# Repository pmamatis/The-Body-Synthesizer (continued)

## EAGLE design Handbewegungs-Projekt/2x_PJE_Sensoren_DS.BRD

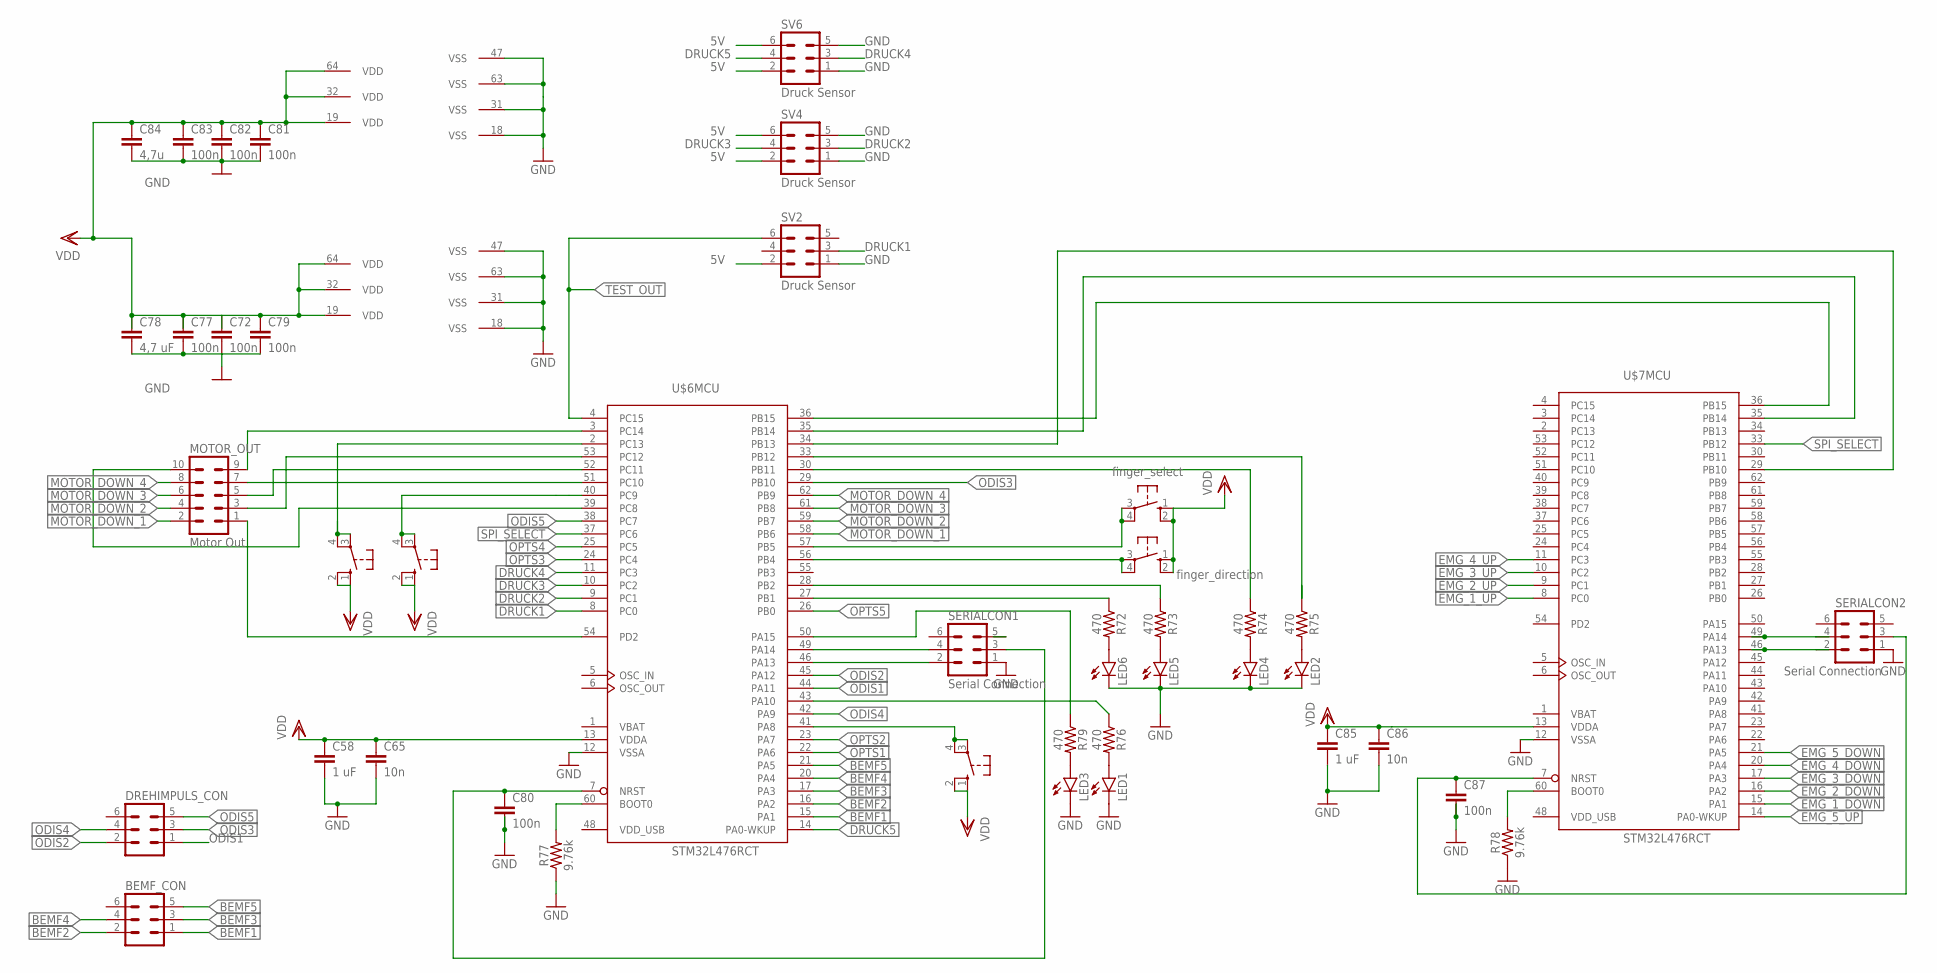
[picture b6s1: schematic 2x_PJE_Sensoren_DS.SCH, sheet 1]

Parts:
BEMF_CON: ML6
BUTTON: 10-XX; B3F-10XX
C58, C85: 1 uF; C0603
C65, C86: 10n; C0603
C72, C77, C79, C80, C81, C82, C83, C87: 100n; C0603
C78: 4,7 uF; C0603
C84: 4,7u; C0603
DREHIMPULS_CON: ML6
FINGER_DIRECTION: finger_direction; B3F-10XX
FINGER_SELECT: finger_select; B3F-10XX
LEARN: 10-XX; B3F-10XX
LEARN_STOP: 10-XX; B3F-10XX
LED1, LED2, LED3, LED4, LED5, LED6: LEDCHIP-LED0603; CHIP-LED0603
MOTOR_OUT: Motor Out; ML10
R72, R73, R74, R75, R76, R79: 470; 0603
R77, R78: 9.76k; 0603
SERIALCON1, SERIALCON2: Serial Connection; ML6
SV2, SV4, SV6: Druck Sensor; ML6
U$6, U$7: STM32L476RCT; LQFP64

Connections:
5V: SV2.2, SV4.2, SV4.6, SV6.2, SV6.6; also elsewhere on the board
BEMF1: BEMF_CON.1, U$6.15 (PA1)
BEMF2: BEMF_CON.2, U$6.16 (PA2)
BEMF3: BEMF_CON.3, U$6.17 (PA3)
BEMF4: BEMF_CON.4, U$6.20 (PA4)
BEMF5: BEMF_CON.5, U$6.21 (PA5)
DRUCK1: SV2.3, U$6.8 (PC0)
DRUCK2: SV4.3, U$6.9 (PC1)
DRUCK3: SV4.4, U$6.10 (PC2)
DRUCK4: SV6.3, U$6.11 (PC3)
DRUCK5: SV6.4, U$6.14 (PA0-WKUP)
EMG_1_DOWN: U$7.15 (PA1); also elsewhere on the board
EMG_1_UP: U$7.8 (PC0); also elsewhere on the board
EMG_2_DOWN: U$7.16 (PA2); also elsewhere on the board
EMG_2_UP: U$7.9 (PC1); also elsewhere on the board
EMG_3_DOWN: U$7.17 (PA3); also elsewhere on the board
EMG_3_UP: U$7.10 (PC2); also elsewhere on the board
EMG_4_DOWN: U$7.20 (PA4)
EMG_4_UP: U$7.11 (PC3)
EMG_5_DOWN: U$7.21 (PA5)
EMG_5_UP: U$7.14 (PA0-WKUP)
GND: C58.2, C65.2, C72.2, C77.2, C78.2, C79.2, C80.2, C81.2, C82.2, C83.2, C84.2, C85.2, C86.2, C87.2, LED1.C, LED2.C, LED3.C, LED4.C, LED5.C, LED6.C, R77.1, R78.1, SERIALCON1.1, SERIALCON2.1, SV2.1, SV4.1, SV4.5, SV6.1, SV6.5, U$6.12 (VSSA), U$6.18 (VSS), U$6.31 (VSS), U$6.47 (VSS), U$6.63 (VSS), U$7.12 (VSSA), U$7.18 (VSS), U$7.31 (VSS), U$7.47 (VSS), U$7.63 (VSS); also elsewhere on the board
LEARN: LEARN.3, LEARN.4 (P1), U$6.41 (PA8)
LEARN1: BUTTON.3, BUTTON.4 (P1), U$6.2 (PC13)
LEARN_STOP: LEARN_STOP.3, LEARN_STOP.4 (P1), U$6.40 (PC9)
LED1: R72.1, U$6.27 (PB1)
LED2: R73.1, U$6.28 (PB2)
LED4: R74.1, U$6.30 (PB11)
LED5: R75.1, U$6.33 (PB12)
MISO: U$6.35 (PB14), U$7.35 (PB14)
MOSI: U$6.36 (PB15), U$7.36 (PB15)
MOTOR_DOWN_1: MOTOR_OUT.2, U$6.58 (PB6)
MOTOR_DOWN_2: MOTOR_OUT.4, U$6.59 (PB7)
MOTOR_DOWN_3: MOTOR_OUT.6, U$6.61 (PB8)
MOTOR_DOWN_4: MOTOR_OUT.8, U$6.62 (PB9)
MOTOR_DOWN_5: MOTOR_OUT.10, U$6.39 (PC8)
MOTOR_UP5: MOTOR_OUT.9, U$6.3 (PC14)
MOTOR_UP_1: MOTOR_OUT.1, U$6.54 (PD2)
MOTOR_UP_2: MOTOR_OUT.3, U$6.53 (PC12)
MOTOR_UP_3: MOTOR_OUT.5, U$6.52 (PC11)
MOTOR_UP_4: MOTOR_OUT.7, U$6.51 (PC10)
unnamed: LED6.A, R72.2
unnamed: LED5.A, R73.2
unnamed: LED4.A, R74.2
unnamed: LED2.A, R75.2
unnamed: LED3.A, R79.2
unnamed: LED1.A, R76.2
unnamed: R76.1, U$6.43 (PA10)
unnamed: FINGER_DIRECTION.3, FINGER_DIRECTION.4 (P1), U$6.56 (PB4)
unnamed: FINGER_SELECT.3, FINGER_SELECT.4 (P1), U$6.57 (PB5)
unnamed: SERIALCON1.4, U$6.49 (PA14)
unnamed: SERIALCON1.2, U$6.46 (PA13)
unnamed: R77.2, U$6.60 (BOOT0)
unnamed: R78.2, U$7.60 (BOOT0)
unnamed: R79.1, U$6.50 (PA15)
NRST1: C80.1, SERIALCON1.3, U$6.7 (NRST)
NRST2: C87.1, SERIALCON2.3, U$7.7 (NRST)
ODIS1: DREHIMPULS_CON.1, U$6.44 (PA11)
ODIS2: DREHIMPULS_CON.2, U$6.45 (PA12)
ODIS3: DREHIMPULS_CON.3, U$6.29 (PB10)
ODIS4: DREHIMPULS_CON.4, U$6.42 (PA9)
ODIS5: DREHIMPULS_CON.5, U$6.38 (PC7)
OPTS1: U$6.22 (PA6); also elsewhere on the board
OPTS2: U$6.23 (PA7); also elsewhere on the board
OPTS3: U$6.24 (PC4); also elsewhere on the board
OPTS4: U$6.25 (PC5); also elsewhere on the board
OPTS5: U$6.26 (PB0); also elsewhere on the board
SPI_CLK: U$6.34 (PB13), U$7.29 (PB10)
SPI_SELECT: U$6.37 (PC6), U$7.33 (PB12)
TCK2: SERIALCON2.4, U$7.49 (PA14)
TEST_OUT: SV2.6, U$6.4 (PC15)
TMS2: SERIALCON2.2, U$7.46 (PA13)
VBAT: U$6.1 (VBAT), U$7.1 (VBAT)
VDD: BUTTON.1 (S), BUTTON.2 (S1), C58.1, C65.1, C72.1, C77.1, C78.1, C79.1, C81.1, C82.1, C83.1, C84.1, C85.1, C86.1, FINGER_DIRECTION.1 (S), FINGER_DIRECTION.2 (S1), FINGER_SELECT.1 (S), FINGER_SELECT.2 (S1), LEARN.1 (S), LEARN.2 (S1), LEARN_STOP.1 (S), LEARN_STOP.2 (S1), U$6.13 (VDDA), U$6.19 (VDD), U$6.32 (VDD), U$6.64 (VDD), U$7.13 (VDDA), U$7.19 (VDD), U$7.32 (VDD), U$7.64 (VDD); also elsewhere on the board
VDD_USB: U$6.48 (VDD_USB), U$7.48 (VDD_USB)

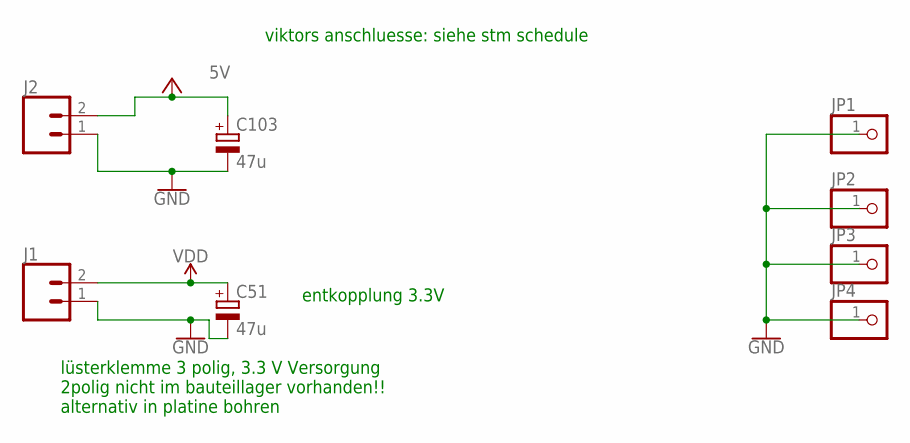
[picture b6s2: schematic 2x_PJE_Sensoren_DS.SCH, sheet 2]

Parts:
C51, C103: 47u; TAP5-70
J1, J2: CONN_02POLAR; MOLEX-1X2
JP1, JP2, JP3, JP4: PINHD-1X1; 1X01

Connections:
5V: C103.+, J2.2; also elsewhere on the board
GND: C51.-, C103.-, J1.1, J2.1, JP1.1, JP2.1, JP3.1, JP4.1; also elsewhere on the board
VDD: C51.+, J1.2; also elsewhere on the board

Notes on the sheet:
viktors anschluesse: siehe stm schedule
entkopplung 3.3V
lüsterklemme 3 polig, 3.3 V Versorgung 2polig nicht im bauteillager vorhanden!! alternativ in platine bohren

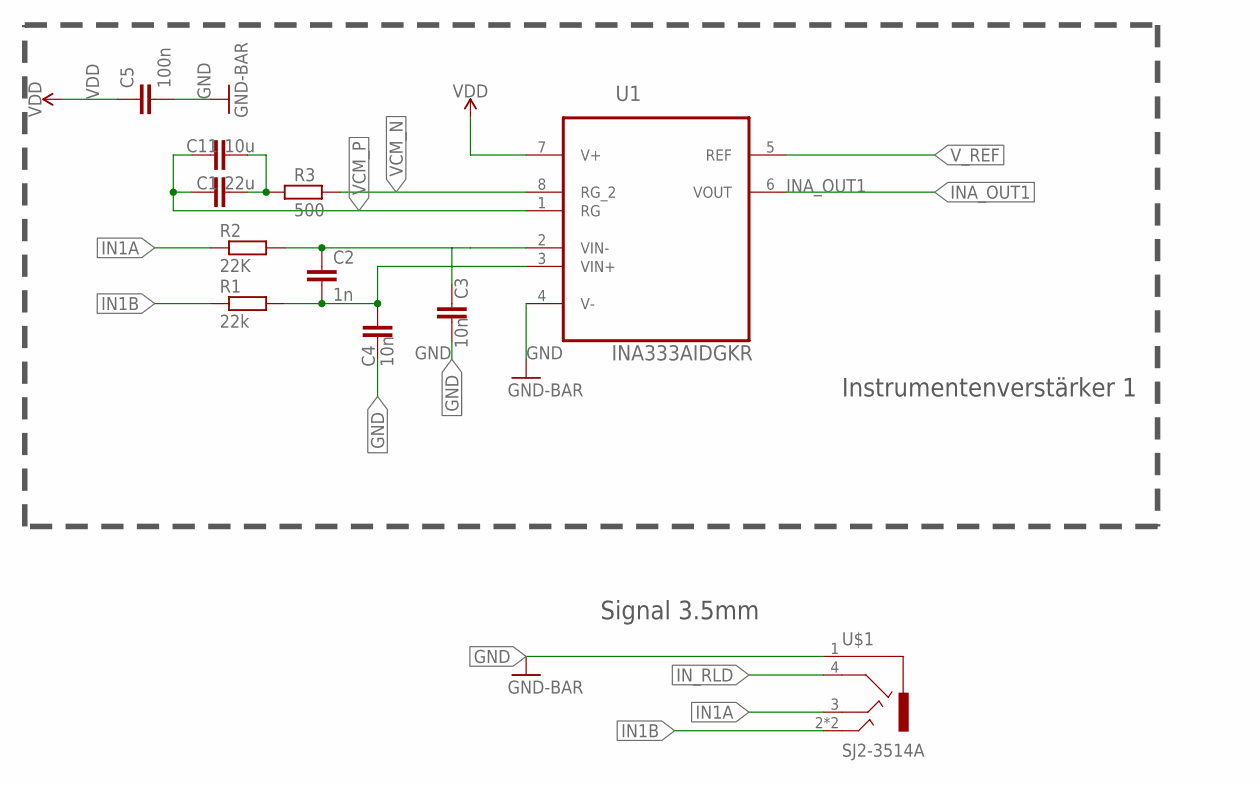
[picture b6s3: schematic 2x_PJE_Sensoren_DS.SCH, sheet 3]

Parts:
C1: 22u; C0603
C2: 1n; C0603
C3, C4: 10n; C0603
C5: 100n; C0603
C11: 10u; C0603
R1: 22k; R0603
R2: 22K; R0603
R3: 500; R0603
U1: INA333AIDGKR; SOP65P490X110-8N
U$1: SJ2-3514A; USR_SJ2-4514A

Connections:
GND: C3.2, C4.2, C5.2, U1.4 (V-), U$1.1; also elsewhere on the board
IN1A: R2.1, U$1.3
IN1B: R1.1, U$1.2, U$1.2_2 (2)
INA_OUT1: U1.6 (VOUT); also elsewhere on the board
IN_RLD: U$1.4; also elsewhere on the board
unnamed: C2.2, C4.1, R1.2, U1.3 (VIN+)
unnamed: C1.2, C11.2, R3.1
unnamed: C2.1, C3.1, R2.2, U1.2 (VIN-)
VCM_N: R3.2, U1.8 (RG_2); also elsewhere on the board
VCM_P: C1.1, C11.1, U1.1 (RG); also elsewhere on the board
VDD: C5.1, U1.7 (V+); also elsewhere on the board
V_REF: U1.5 (REF); also elsewhere on the board

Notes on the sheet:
Instrumentenverstärker 1
Signal 3.5mm

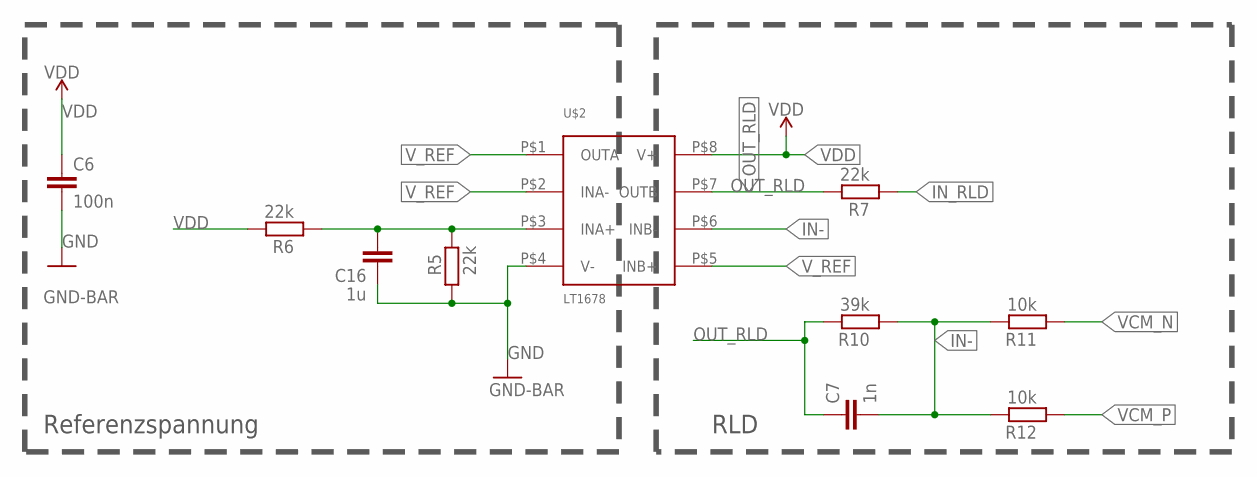
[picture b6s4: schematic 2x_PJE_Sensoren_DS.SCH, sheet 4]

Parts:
C6: 100n; C0603
C7: 1n; C0603
C16: 1u; C0603
R5, R6, R7: 22k; R0603
R10: 39k; R0603
R11, R12: 10k; R0603
U$2: LT1678; S8

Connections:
GND: C6.2, C16.1, R5.1, U$2.P$4 (V-); also elsewhere on the board
IN-: C7.2, R10.1, R11.2, R12.2, U$2.P$6 (INB-)
IN_RLD: R7.1; also elsewhere on the board
unnamed: C16.2, R5.2, R6.1, U$2.P$3 (INA+)
OUT_RLD: C7.1, R7.2, R10.2, U$2.P$7 (OUTB)
VCM_N: R11.1; also elsewhere on the board
VCM_P: R12.1; also elsewhere on the board
VDD: C6.1, R6.2, U$2.P$8 (V+); also elsewhere on the board
V_REF: U$2.P$1 (OUTA), U$2.P$2 (INA-), U$2.P$5 (INB+); also elsewhere on the board

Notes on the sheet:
Referenzspannung
RLD

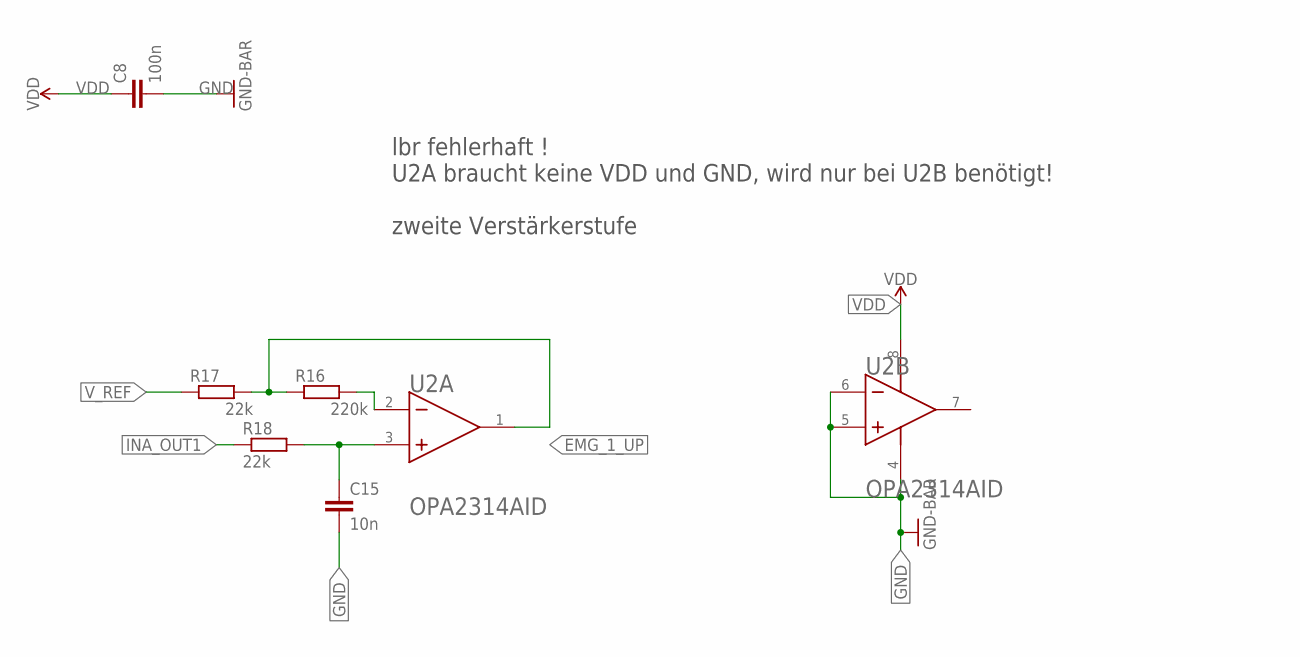
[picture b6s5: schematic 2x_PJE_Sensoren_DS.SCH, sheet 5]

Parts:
C8: 100n; C0603
C15: 10n; C0603
R16: 220k; R0603
R17, R18: 22k; R0603
U2: TEXAS_INSTRUMENTS_OPA2314AIDTEXAS_INSTRUMENTS_OPA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; TEXAS_INSTRUMENTS_OPA2314AID_0

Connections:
EMG_1_UP: R16.1, R17.2, U2.1 (OUT_A); also elsewhere on the board
GND: C8.2, C15.2, U2.4 (V-), U2.5 (IN_B+), U2.6 (IN_B-); also elsewhere on the board
INA_OUT1: R18.1; also elsewhere on the board
unnamed: R16.2, U2.2 (IN_A-)
unnamed: C15.1, R18.2, U2.3 (IN_A+)
VDD: C8.1, U2.8 (V+); also elsewhere on the board
V_REF: R17.1; also elsewhere on the board

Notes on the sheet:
lbr fehlerhaft ! U2A braucht keine VDD und GND, wird nur bei U2B benötigt! zweite Verstärkerstufe

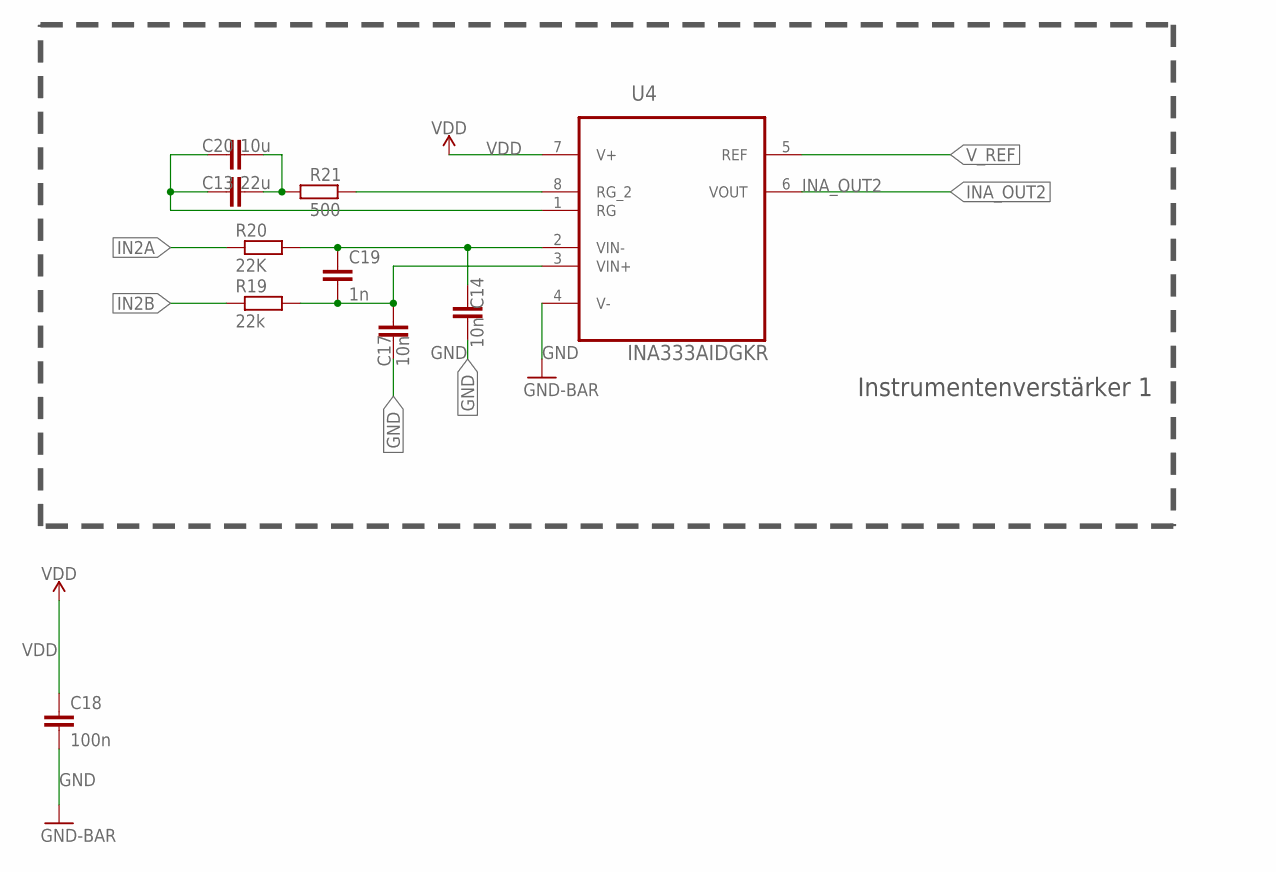
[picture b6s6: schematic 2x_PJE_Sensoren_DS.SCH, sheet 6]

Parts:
C13: 22u; C0603
C14, C17: 10n; C0603
C18: 100n; C0603
C19: 1n; C0603
C20: 10u; C0603
R19: 22k; R0603
R20: 22K; R0603
R21: 500; R0603
U4: INA333AIDGKR; SOP65P490X110-8N

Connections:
GND: C14.2, C17.2, C18.2, U4.4 (V-); also elsewhere on the board
IN2A: R20.1; also elsewhere on the board
IN2B: R19.1; also elsewhere on the board
INA_OUT2: U4.6 (VOUT); also elsewhere on the board
unnamed: C13.2, C20.2, R21.1
unnamed: R21.2, U4.8 (RG_2)
unnamed: C13.1, C20.1, U4.1 (RG)
unnamed: C14.1, C19.1, R20.2, U4.2 (VIN-)
unnamed: C17.1, C19.2, R19.2, U4.3 (VIN+)
VDD: C18.1, U4.7 (V+); also elsewhere on the board
V_REF: U4.5 (REF); also elsewhere on the board

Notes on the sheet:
Instrumentenverstärker 1

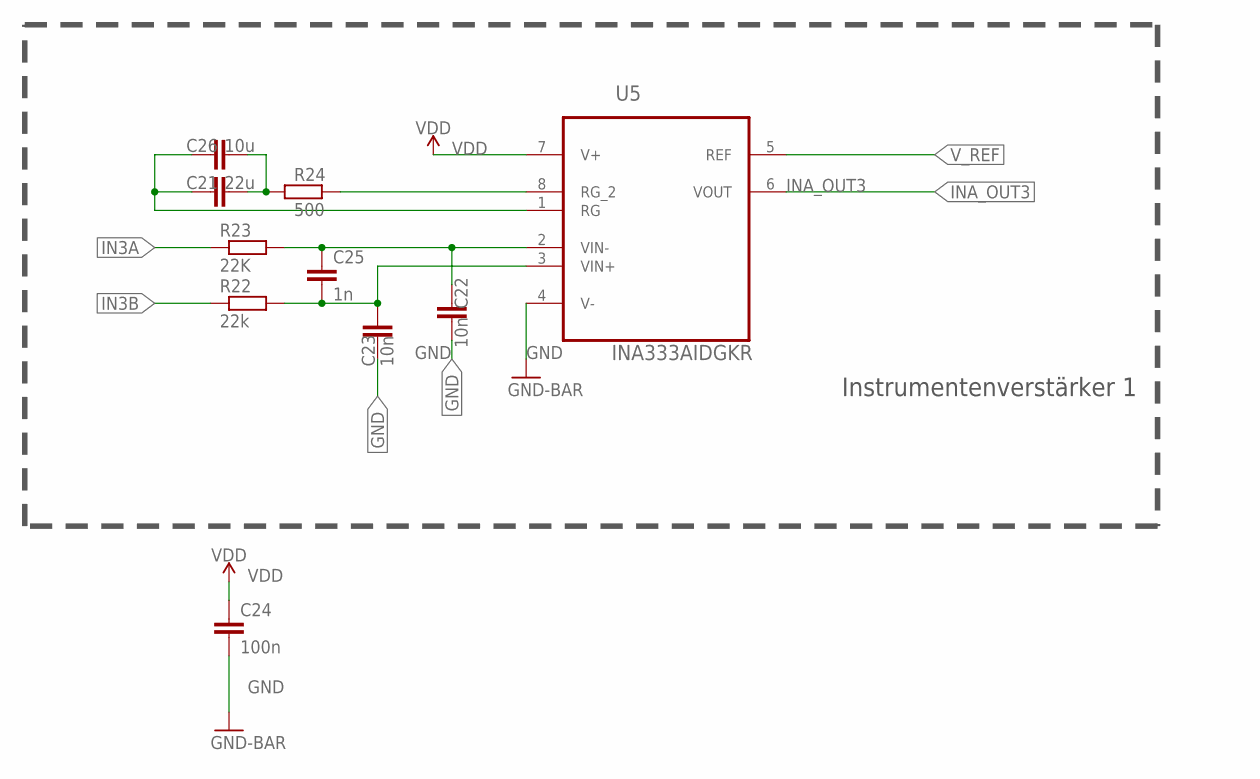
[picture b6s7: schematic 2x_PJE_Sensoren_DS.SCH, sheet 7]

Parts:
C21: 22u; C0603
C22, C23: 10n; C0603
C24: 100n; C0603
C25: 1n; C0603
C26: 10u; C0603
R22: 22k; R0603
R23: 22K; R0603
R24: 500; R0603
U5: INA333AIDGKR; SOP65P490X110-8N

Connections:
GND: C22.2, C23.2, C24.2, U5.4 (V-); also elsewhere on the board
IN3A: R23.1; also elsewhere on the board
IN3B: R22.1; also elsewhere on the board
INA_OUT3: U5.6 (VOUT); also elsewhere on the board
unnamed: C21.2, C26.2, R24.1
unnamed: R24.2, U5.8 (RG_2)
unnamed: C21.1, C26.1, U5.1 (RG)
unnamed: C22.1, C25.1, R23.2, U5.2 (VIN-)
unnamed: C23.1, C25.2, R22.2, U5.3 (VIN+)
VDD: C24.1, U5.7 (V+); also elsewhere on the board
V_REF: U5.5 (REF); also elsewhere on the board

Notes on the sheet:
Instrumentenverstärker 1

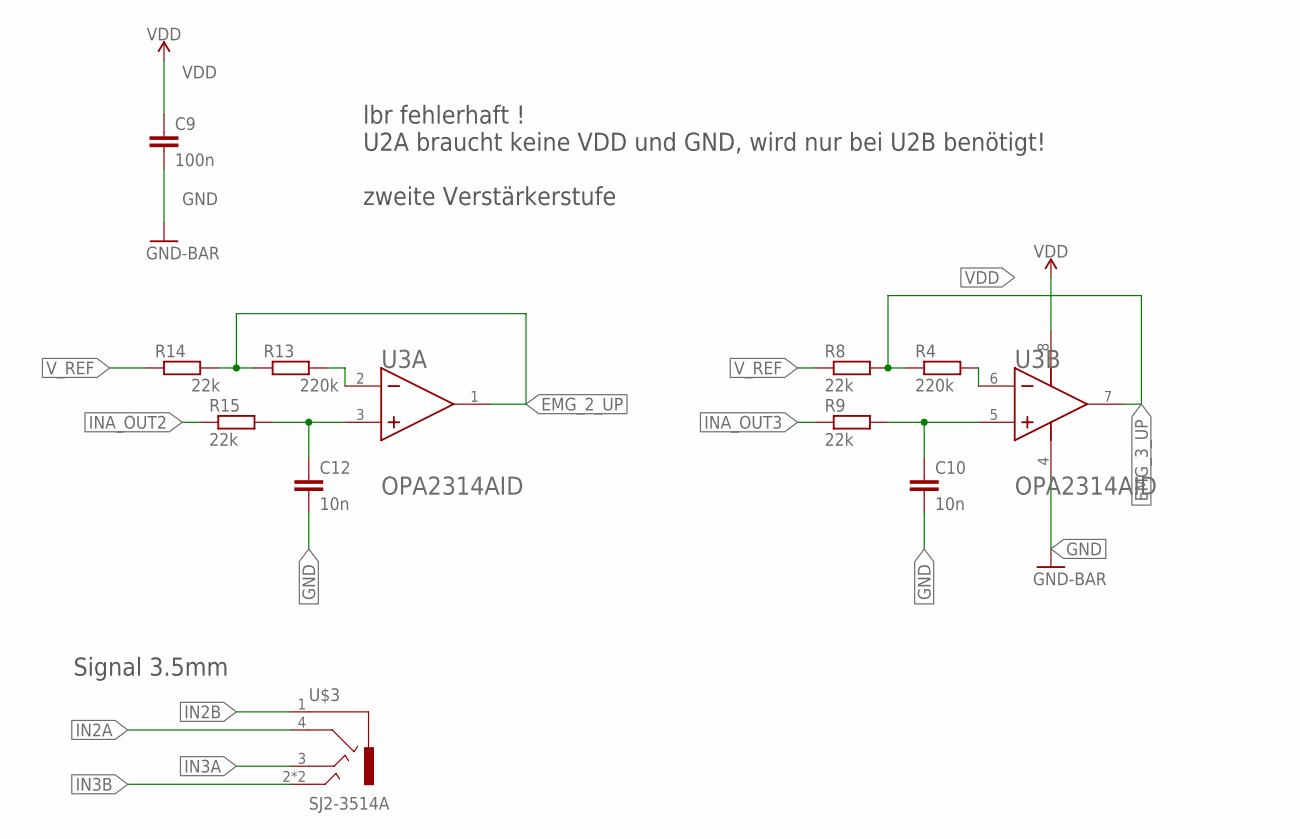
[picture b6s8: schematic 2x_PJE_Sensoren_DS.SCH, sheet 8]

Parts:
C9: 100n; C0603
C10, C12: 10n; C0603
R4, R13: 220k; R0603
R8, R9, R14, R15: 22k; R0603
U3: TEXAS_INSTRUMENTS_OPA2314AIDTEXAS_INSTRUMENTS_OPA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; TEXAS_INSTRUMENTS_OPA2314AID_0
U$3: SJ2-3514A; USR_SJ2-4514A

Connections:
EMG_2_UP: R13.1, R14.2, U3.1 (OUT_A); also elsewhere on the board
EMG_3_UP: R4.1, R8.2, U3.7 (OUT_B); also elsewhere on the board
GND: C9.2, C10.2, C12.2, U3.4 (V-); also elsewhere on the board
IN2A: U$3.4; also elsewhere on the board
IN2B: U$3.1; also elsewhere on the board
IN3A: U$3.3; also elsewhere on the board
IN3B: U$3.2, U$3.2_2 (2); also elsewhere on the board
INA_OUT2: R15.1; also elsewhere on the board
INA_OUT3: R9.1; also elsewhere on the board
unnamed: C10.1, R9.2, U3.5 (IN_B+)
unnamed: R4.2, U3.6 (IN_B-)
unnamed: C12.1, R15.2, U3.3 (IN_A+)
unnamed: R13.2, U3.2 (IN_A-)
VDD: C9.1, U3.8 (V+); also elsewhere on the board
V_REF: R8.1, R14.1; also elsewhere on the board

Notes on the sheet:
lbr fehlerhaft ! U2A braucht keine VDD und GND, wird nur bei U2B benötigt! zweite Verstärkerstufe
Signal 3.5mm

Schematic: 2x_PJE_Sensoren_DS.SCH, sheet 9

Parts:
C30: 22u; C0603
C31, C32: 10n; C0603
C33: 100n; C0603
C34: 1n; C0603
C35: 10u; C0603
R31: 22k; R0603
R32: 22K; R0603
R33: 500; R0603
U7: INA333AIDGKR; SOP65P490X110-8N

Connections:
GND: C31.2, C32.2, C33.2, U7.4 (V-); also elsewhere on the board
IN4A: R32.1; also elsewhere on the board
IN4B: R31.1; also elsewhere on the board
INA_OUT4: U7.6 (VOUT); also elsewhere on the board
unnamed: C30.2, C35.2, R33.1
unnamed: R33.2, U7.8 (RG_2)
unnamed: C30.1, C35.1, U7.1 (RG)
unnamed: C31.1, C34.1, R32.2, U7.2 (VIN-)
unnamed: C32.1, C34.2, R31.2, U7.3 (VIN+)
VDD: C33.1, U7.7 (V+); also elsewhere on the board
V_REF: U7.5 (REF); also elsewhere on the board

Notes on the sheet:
Instrumentenverstärker 1

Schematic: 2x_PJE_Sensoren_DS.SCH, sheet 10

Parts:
C36: 22u; C0603
C37, C38: 10n; C0603
C39: 100n; C0603
C40: 1n; C0603
C41: 10u; C0603
R34: 22k; R0603
R35: 22K; R0603
R36: 500; R0603
U8: INA333AIDGKR; SOP65P490X110-8N

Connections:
GND: C37.2, C38.2, C39.2, U8.4 (V-); also elsewhere on the board
IN5A: R35.1; also elsewhere on the board
IN5B: R34.1; also elsewhere on the board
INA_OUT5: U8.6 (VOUT); also elsewhere on the board
unnamed: C36.2, C41.2, R36.1
unnamed: R36.2, U8.8 (RG_2)
unnamed: C36.1, C41.1, U8.1 (RG)
unnamed: C37.1, C40.1, R35.2, U8.2 (VIN-)
unnamed: C38.1, C40.2, R34.2, U8.3 (VIN+)
VDD: C39.1, U8.7 (V+); also elsewhere on the board
V_REF: U8.5 (REF); also elsewhere on the board

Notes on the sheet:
Instrumentenverstärker 1

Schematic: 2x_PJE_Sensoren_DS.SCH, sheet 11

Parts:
C27: 100n; C0603
C28, C29: 10n; C0603
R25, R28: 220k; R0603
R26, R27, R29, R30: 22k; R0603
U6: TEXAS_INSTRUMENTS_OPA2314AIDTEXAS_INSTRUMENTS_OPA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; TEXAS_INSTRUMENTS_OPA2314AID_0
U$4: SJ2-3514A; USR_SJ2-4514A

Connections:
EMG_1_DOWN: R28.1, R29.2, U6.1 (OUT_A); also elsewhere on the board
EMG_2_DOWN: R25.1, R26.2, U6.7 (OUT_B); also elsewhere on the board
GND: C27.2, C28.2, C29.2, U6.4 (V-); also elsewhere on the board
IN4A: U$4.4; also elsewhere on the board
IN4B: U$4.1; also elsewhere on the board
IN5A: U$4.3; also elsewhere on the board
IN5B: U$4.2, U$4.2_2 (2); also elsewhere on the board
INA_OUT4: R30.1; also elsewhere on the board
INA_OUT5: R27.1; also elsewhere on the board
unnamed: C28.1, R27.2, U6.5 (IN_B+)
unnamed: R25.2, U6.6 (IN_B-)
unnamed: C29.1, R30.2, U6.3 (IN_A+)
unnamed: R28.2, U6.2 (IN_A-)
VDD: C27.1, U6.8 (V+); also elsewhere on the board
V_REF: R26.1, R29.1; also elsewhere on the board

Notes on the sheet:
lbr fehlerhaft ! U2A braucht keine VDD und GND, wird nur bei U2B benötigt! zweite Verstärkerstufe
Signal 3.5mm

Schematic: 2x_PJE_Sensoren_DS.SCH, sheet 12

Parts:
C91: 22u; C0603
C92, C93: 10n; C0603
C94: 100n; C0603
C95: 1n; C0603
C96: 10u; C0603
R86: 22k; R0603
R87: 22K; R0603
R88: 500; R0603
U20: INA333AIDGKR; SOP65P490X110-8N

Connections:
GND: C92.2, C93.2, C94.2, U20.4 (V-); also elsewhere on the board
IN6A: R87.1; also elsewhere on the board
IN6B: R86.1; also elsewhere on the board
INA_OUT6: U20.6 (VOUT); also elsewhere on the board
unnamed: C91.2, C96.2, R88.1
unnamed: R88.2, U20.8 (RG_2)
unnamed: C91.1, C96.1, U20.1 (RG)
unnamed: C92.1, C95.1, R87.2, U20.2 (VIN-)
unnamed: C93.1, C95.2, R86.2, U20.3 (VIN+)
VDD: C94.1, U20.7 (V+); also elsewhere on the board
V_REF: U20.5 (REF); also elsewhere on the board

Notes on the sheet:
Instrumentenverstärker 1

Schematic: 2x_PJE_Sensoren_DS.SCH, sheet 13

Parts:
C97: 22u; C0603
C98, C99: 10n; C0603
C100: 100n; C0603
C101: 1n; C0603
C102: 10u; C0603
R89: 22k; R0603
R90: 22K; R0603
R91: 500; R0603
U21: INA333AIDGKR; SOP65P490X110-8N

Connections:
GND: C98.2, C99.2, C100.2, U21.4 (V-); also elsewhere on the board
IN7A: R90.1; also elsewhere on the board
IN7B: R89.1; also elsewhere on the board
INA_OUT7: U21.6 (VOUT); also elsewhere on the board
unnamed: C97.2, C102.2, R91.1
unnamed: R91.2, U21.8 (RG_2)
unnamed: C97.1, C102.1, U21.1 (RG)
unnamed: C98.1, C101.1, R90.2, U21.2 (VIN-)
unnamed: C99.1, C101.2, R89.2, U21.3 (VIN+)
VDD: C100.1, U21.7 (V+); also elsewhere on the board
V_REF: U21.5 (REF); also elsewhere on the board

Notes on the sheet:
Instrumentenverstärker 1

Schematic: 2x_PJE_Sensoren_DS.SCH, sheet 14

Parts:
C88: 100n; C0603
C89, C90: 10n; C0603
R80, R83: 220k; R0603
R81, R82, R84, R85: 22k; R0603
U19: TEXAS_INSTRUMENTS_OPA2314AIDTEXAS_INSTRUMENTS_OPA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; TEXAS_INSTRUMENTS_OPA2314AID_0
U$8: SJ2-3514A; USR_SJ2-4514A

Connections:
ADC7: R80.1, R81.2, U19.7 (OUT_B)
EMG_3_DOWN: R83.1, R84.2, U19.1 (OUT_A); also elsewhere on the board
GND: C88.2, C89.2, C90.2, U19.4 (V-); also elsewhere on the board
IN6A: U$8.4; also elsewhere on the board
IN6B: U$8.1; also elsewhere on the board
IN7A: U$8.3; also elsewhere on the board
IN7B: U$8.2, U$8.2_2 (2); also elsewhere on the board
INA_OUT6: R85.1; also elsewhere on the board
INA_OUT7: R82.1; also elsewhere on the board
unnamed: C89.1, R82.2, U19.5 (IN_B+)
unnamed: R80.2, U19.6 (IN_B-)
unnamed: C90.1, R85.2, U19.3 (IN_A+)
unnamed: R83.2, U19.2 (IN_A-)
VDD: C88.1, U19.8 (V+); also elsewhere on the board
V_REF: R81.1, R84.1; also elsewhere on the board

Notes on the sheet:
lbr fehlerhaft ! U2A braucht keine VDD und GND, wird nur bei U2B benötigt! zweite Verstärkerstufe
Signal 3.5mm

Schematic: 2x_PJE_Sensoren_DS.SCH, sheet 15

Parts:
C42: 470n; C0603
C43: 47µ; C0603
C44: 1µ; C0603
C45, C46: 100n; C0603
C47, C48: 0,47u; C0603
R37: 1M; R0603
R38, R41: 680k; R0603
R39: 120; R0603
R40: 168k; R0603
R42: 1k; R0603
R43: 560; R0603
SS: PINHD-1X3; 1X03
U9, U10: TEXAS_INSTRUMENTS_OPA2314AIDTEXAS_INSTRUMENTS_OPA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; TEXAS_INSTRUMENTS_OPA2314AID_0
U$5: MAX6018X_MAX6018X; MAX6018X_SOT-3

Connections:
+5V/2: R38.1, R39.1, R41.2, R42.2, U$5.OUT; also elsewhere on the board
GND: C44.2, C45.2, C46.1, SS.2, U9.2 (IN_A-), U9.3 (IN_A+), U9.4 (V-), U10.4 (V-), U10.5 (IN_B+), U$5.GND; also elsewhere on the board
INPUT1: R37.1, SS.3, U10.6 (IN_B-)
unnamed: C47.2, R38.2, U9.5 (IN_B+)
unnamed: C42.2, R39.2, R40.1, U9.6 (IN_B-)
unnamed: C42.1, C48.1, R40.2, U9.7 (OUT_B)
unnamed: C48.2, R41.1, U10.3 (IN_A+)
unnamed: C47.1, R37.2, U10.7 (OUT_B)
unnamed: C43.1, R42.1, R43.2, U10.2 (IN_A-)
OPTS1: C43.2, R43.1, U10.1 (OUT_A); also elsewhere on the board
VDD: C44.1, C45.1, C46.2, SS.1, U9.8 (V+), U10.8 (V+), U$5.IN; also elsewhere on the board

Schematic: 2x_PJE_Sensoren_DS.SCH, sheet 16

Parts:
C49: 470n; C0603
C50: 47µ; C0603
C52, C53: 100n; C0603
C54, C55: 0,47u; C0603
R44: 1M; R0603
R45, R48: 680k; R0603
R46: 120; R0603
R47: 168k; R0603
R49: 1k; R0603
R50: 560; R0603
SS1: PINHD-1X3; 1X03
U11, U12: TEXAS_INSTRUMENTS_OPA2314AIDTEXAS_INSTRUMENTS_OPA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; TEXAS_INSTRUMENTS_OPA2314AID_0

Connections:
+5V/2: R45.1, R46.1, R48.2, R49.2; also elsewhere on the board
GND: C52.2, C53.1, SS1.2, U11.2 (IN_A-), U11.3 (IN_A+), U11.4 (V-), U12.4 (V-), U12.5 (IN_B+); also elsewhere on the board
INPUT2: R44.1, SS1.3, U12.6 (IN_B-)
unnamed: C54.2, R45.2, U11.5 (IN_B+)
unnamed: C49.2, R46.2, R47.1, U11.6 (IN_B-)
unnamed: C49.1, C55.1, R47.2, U11.7 (OUT_B)
unnamed: C55.2, R48.1, U12.3 (IN_A+)
unnamed: C54.1, R44.2, U12.7 (OUT_B)
unnamed: C50.1, R49.1, R50.2, U12.2 (IN_A-)
OPTS2: C50.2, R50.1, U12.1 (OUT_A); also elsewhere on the board
VDD: C52.1, C53.2, SS1.1, U11.8 (V+), U12.8 (V+); also elsewhere on the board

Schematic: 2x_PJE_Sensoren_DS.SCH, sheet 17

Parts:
C56: 470n; C0603
C57: 47µ; C0603
C59, C60: 100n; C0603
C61, C62: 0,47u; C0603
R51: 1M; R0603
R52, R55: 680k; R0603
R53: 120; R0603
R54: 168k; R0603
R56: 1k; R0603
R57: 560; R0603
SS2: PINHD-1X3; 1X03
U13, U14: TEXAS_INSTRUMENTS_OPA2314AIDTEXAS_INSTRUMENTS_OPA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; TEXAS_INSTRUMENTS_OPA2314AID_0

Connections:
+5V/2: R52.1, R53.1, R55.2, R56.2; also elsewhere on the board
GND: C59.2, C60.1, SS2.2, U13.2 (IN_A-), U13.3 (IN_A+), U13.4 (V-), U14.4 (V-), U14.5 (IN_B+); also elsewhere on the board
INPUT3: R51.1, SS2.3, U14.6 (IN_B-)
unnamed: C61.2, R52.2, U13.5 (IN_B+)
unnamed: C56.2, R53.2, R54.1, U13.6 (IN_B-)
unnamed: C56.1, C62.1, R54.2, U13.7 (OUT_B)
unnamed: C62.2, R55.1, U14.3 (IN_A+)
unnamed: C61.1, R51.2, U14.7 (OUT_B)
unnamed: C57.1, R56.1, R57.2, U14.2 (IN_A-)
OPTS3: C57.2, R57.1, U14.1 (OUT_A); also elsewhere on the board
VDD: C59.1, C60.2, SS2.1, U13.8 (V+), U14.8 (V+); also elsewhere on the board

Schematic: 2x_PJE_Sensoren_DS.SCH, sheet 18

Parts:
C63: 470n; C0603
C64: 47µ; C0603
C66, C67: 100n; C0603
C68, C69: 0,47u; C0603
R58: 1M; R0603
R59, R62: 680k; R0603
R60: 120; R0603
R61: 168k; R0603
R63: 1k; R0603
R64: 560; R0603
SS3: PINHD-1X3; 1X03
U15, U16: TEXAS_INSTRUMENTS_OPA2314AIDTEXAS_INSTRUMENTS_OPA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; TEXAS_INSTRUMENTS_OPA2314AID_0

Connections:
+5V/2: R59.1, R60.1, R62.2, R63.2; also elsewhere on the board
GND: C66.2, C67.1, SS3.2, U15.2 (IN_A-), U15.3 (IN_A+), U15.4 (V-), U16.4 (V-), U16.5 (IN_B+); also elsewhere on the board
INPUT4: R58.1, SS3.3, U16.6 (IN_B-)
unnamed: C68.2, R59.2, U15.5 (IN_B+)
unnamed: C63.2, R60.2, R61.1, U15.6 (IN_B-)
unnamed: C63.1, C69.1, R61.2, U15.7 (OUT_B)
unnamed: C69.2, R62.1, U16.3 (IN_A+)
unnamed: C68.1, R58.2, U16.7 (OUT_B)
unnamed: C64.1, R63.1, R64.2, U16.2 (IN_A-)
OPTS4: C64.2, R64.1, U16.1 (OUT_A); also elsewhere on the board
VDD: C66.1, C67.2, SS3.1, U15.8 (V+), U16.8 (V+); also elsewhere on the board

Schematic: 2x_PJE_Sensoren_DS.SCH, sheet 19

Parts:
C70: 470n; C0603
C71: 47µ; C0603
C73, C74: 100n; C0603
C75, C76: 0,47u; C0603
R65: 1M; R0603
R66, R69: 680k; R0603
R67: 120; R0603
R68: 168k; R0603
R70: 1k; R0603
R71: 560; R0603
SS4: PINHD-1X3; 1X03
U17, U18: TEXAS_INSTRUMENTS_OPA2314AIDTEXAS_INSTRUMENTS_OPA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; TEXAS_INSTRUMENTS_OPA2314AID_0

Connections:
+5V/2: R66.1, R67.1, R69.2, R70.2; also elsewhere on the board
GND: C73.2, C74.1, SS4.2, U17.2 (IN_A-), U17.3 (IN_A+), U17.4 (V-), U18.4 (V-), U18.5 (IN_B+); also elsewhere on the board
INPUT5: R65.1, SS4.3, U18.6 (IN_B-)
unnamed: C75.2, R66.2, U17.5 (IN_B+)
unnamed: C70.2, R67.2, R68.1, U17.6 (IN_B-)
unnamed: C70.1, C76.1, R68.2, U17.7 (OUT_B)
unnamed: C76.2, R69.1, U18.3 (IN_A+)
unnamed: C75.1, R65.2, U18.7 (OUT_B)
unnamed: C71.1, R70.1, R71.2, U18.2 (IN_A-)
OPTS5: C71.2, R71.1, U18.1 (OUT_A); also elsewhere on the board
VDD: C73.1, C74.2, SS4.1, U17.8 (V+), U18.8 (V+); also elsewhere on the board

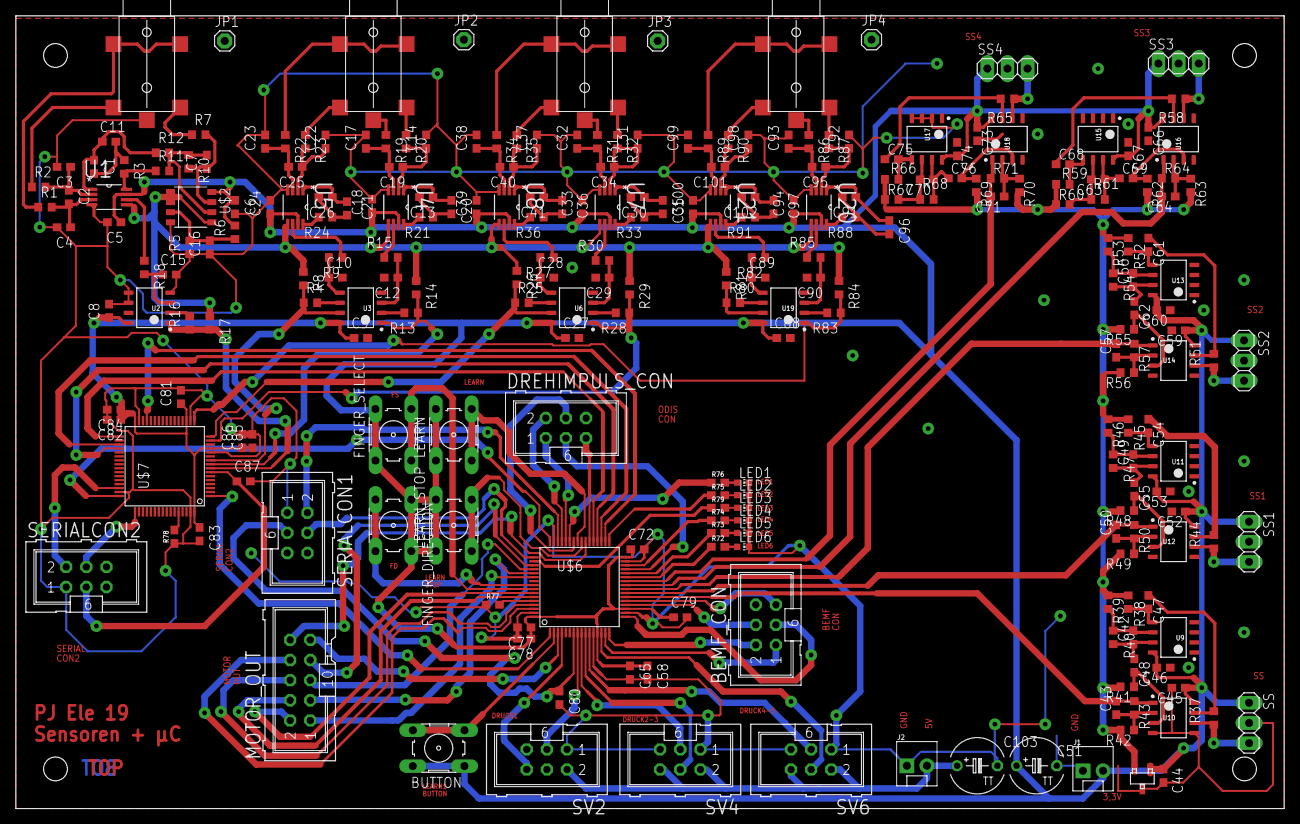
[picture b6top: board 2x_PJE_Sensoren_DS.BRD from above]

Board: 2 copper layers, 160.0 x 100.0 mm, 253 parts (0 on the bottom side), 183 nets.

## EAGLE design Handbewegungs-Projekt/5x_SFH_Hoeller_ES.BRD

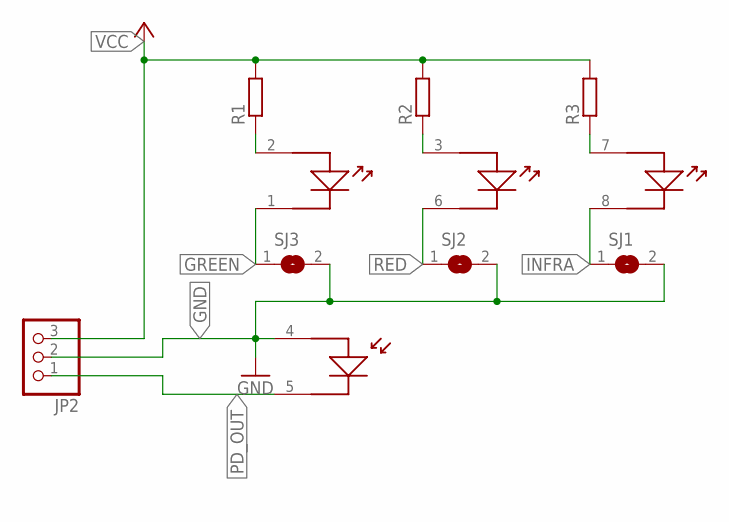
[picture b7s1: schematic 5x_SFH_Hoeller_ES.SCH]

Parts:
JP2: PINHD-1X3; 1X03
PD-: SFH7050_SFH7050
R1, R2, R3: R-EU_R0603; R0603
SJ1, SJ2, SJ3: SJ

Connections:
GND: JP2.2, PD-.4 (A), SJ1.2, SJ2.2, SJ3.2
GREEN: PD-.1 (C), SJ3.1
INFRA: PD-.8 (C), SJ1.1
unnamed: PD-.2 (A), R1.1
unnamed: PD-.3 (A), R2.1
unnamed: PD-.7 (A), R3.1
PD_OUT: JP2.1, PD-.5 (C)
RED: PD-.6 (C), SJ2.1
VCC: JP2.3, R1.2, R2.2, R3.2

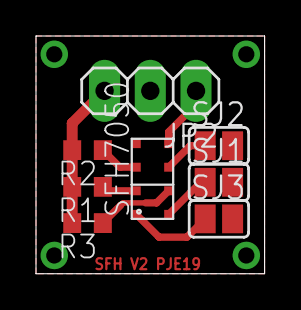
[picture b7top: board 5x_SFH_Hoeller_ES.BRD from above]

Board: 2 copper layers, 12.7 x 13.2 mm, 8 parts (0 on the bottom side), 9 nets.
